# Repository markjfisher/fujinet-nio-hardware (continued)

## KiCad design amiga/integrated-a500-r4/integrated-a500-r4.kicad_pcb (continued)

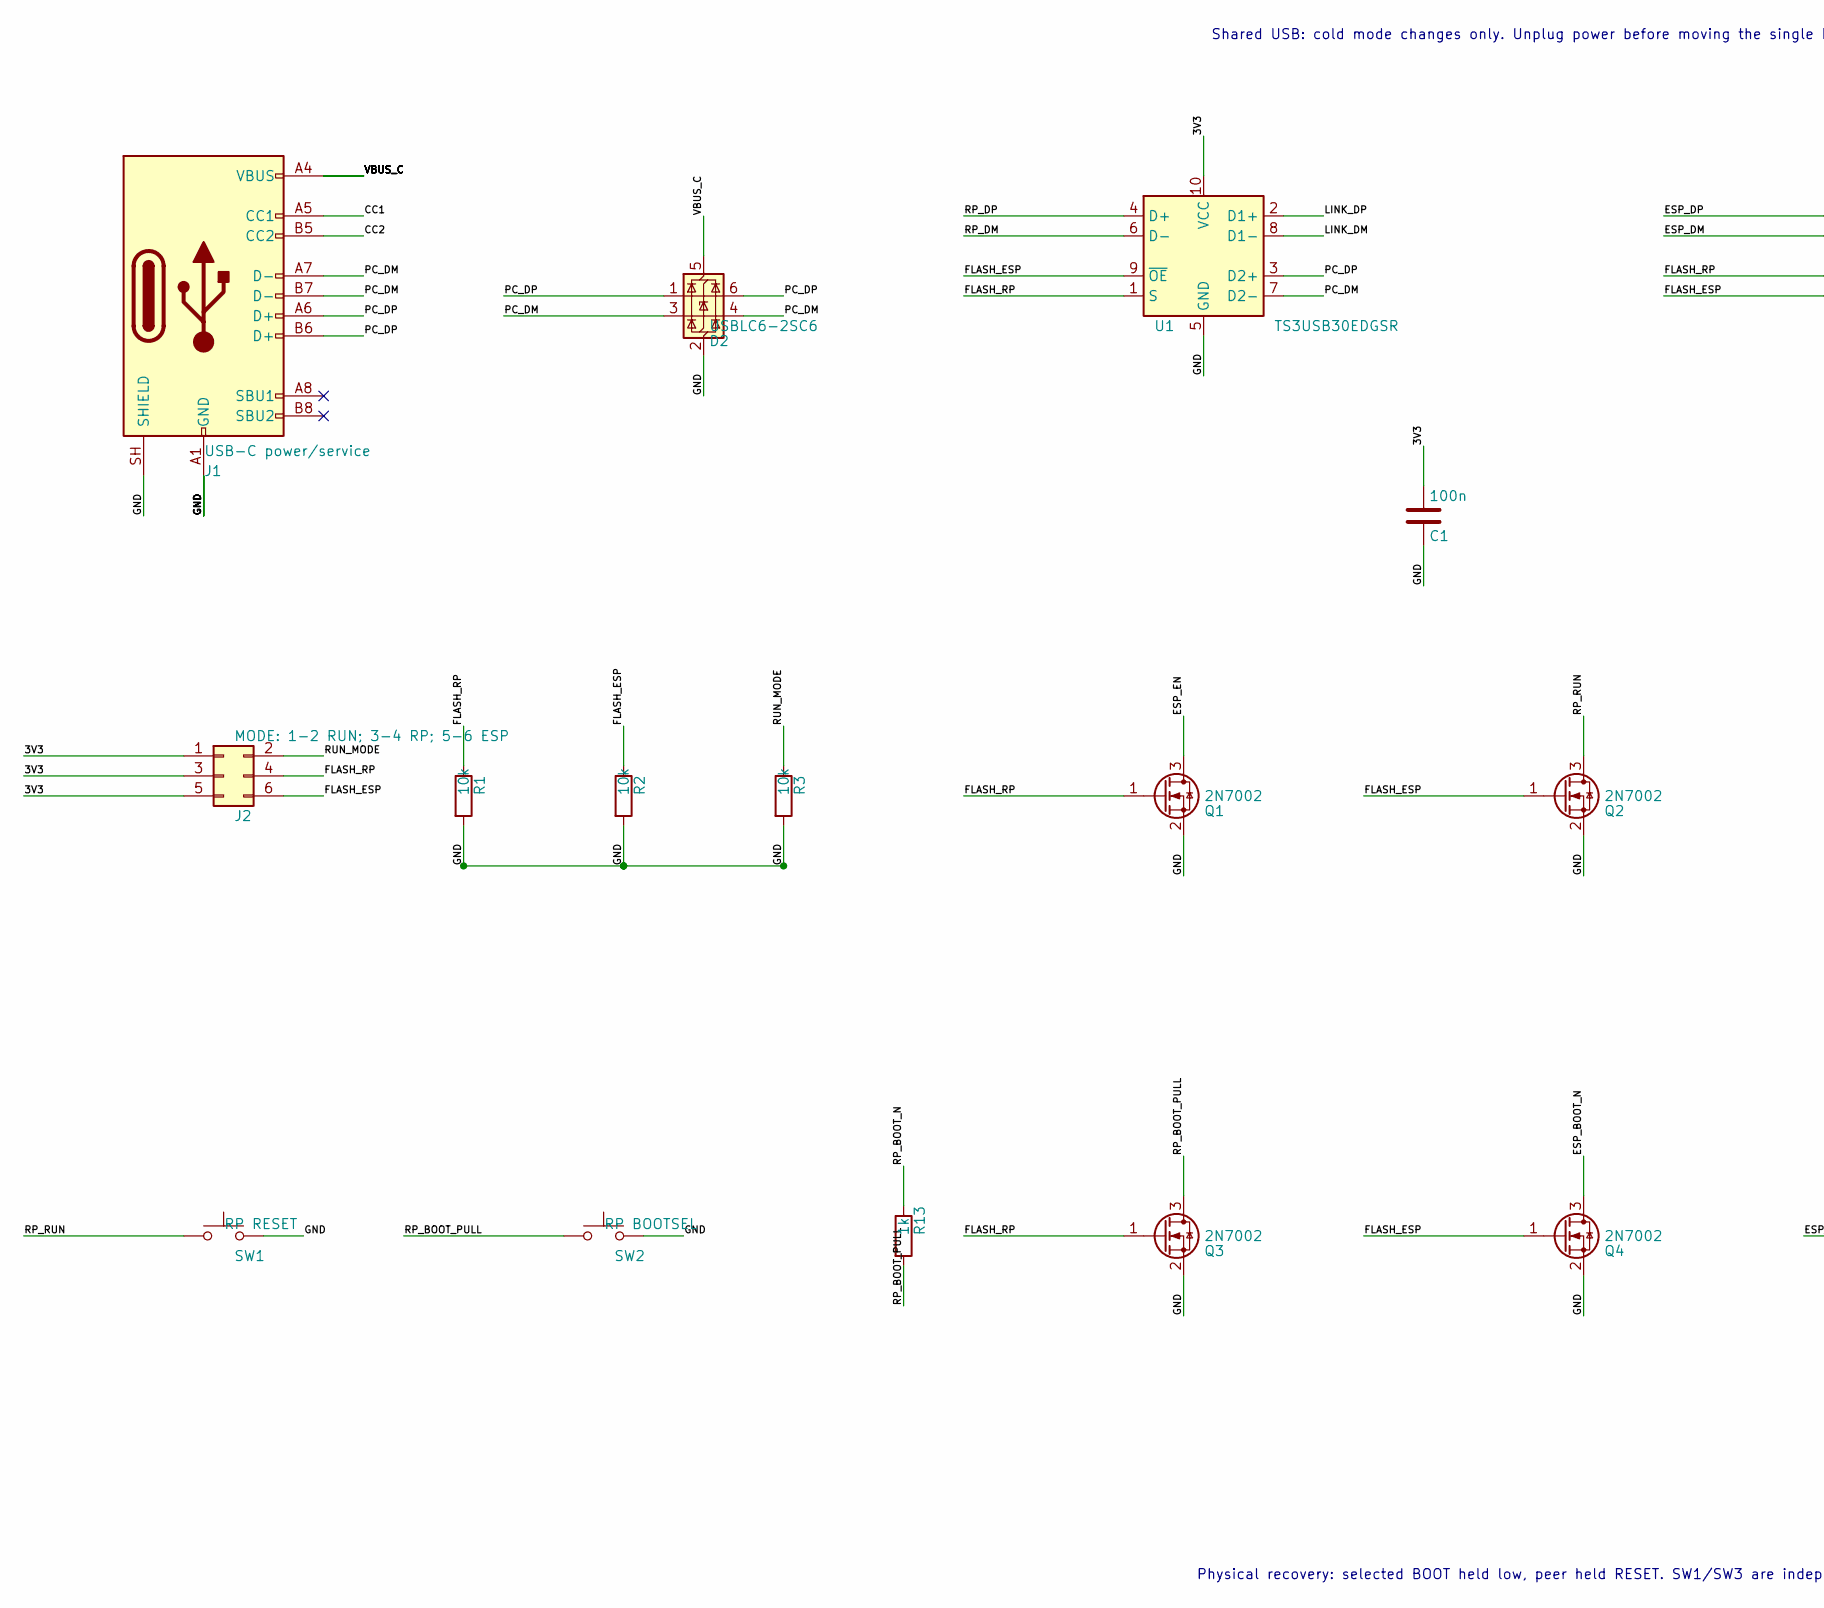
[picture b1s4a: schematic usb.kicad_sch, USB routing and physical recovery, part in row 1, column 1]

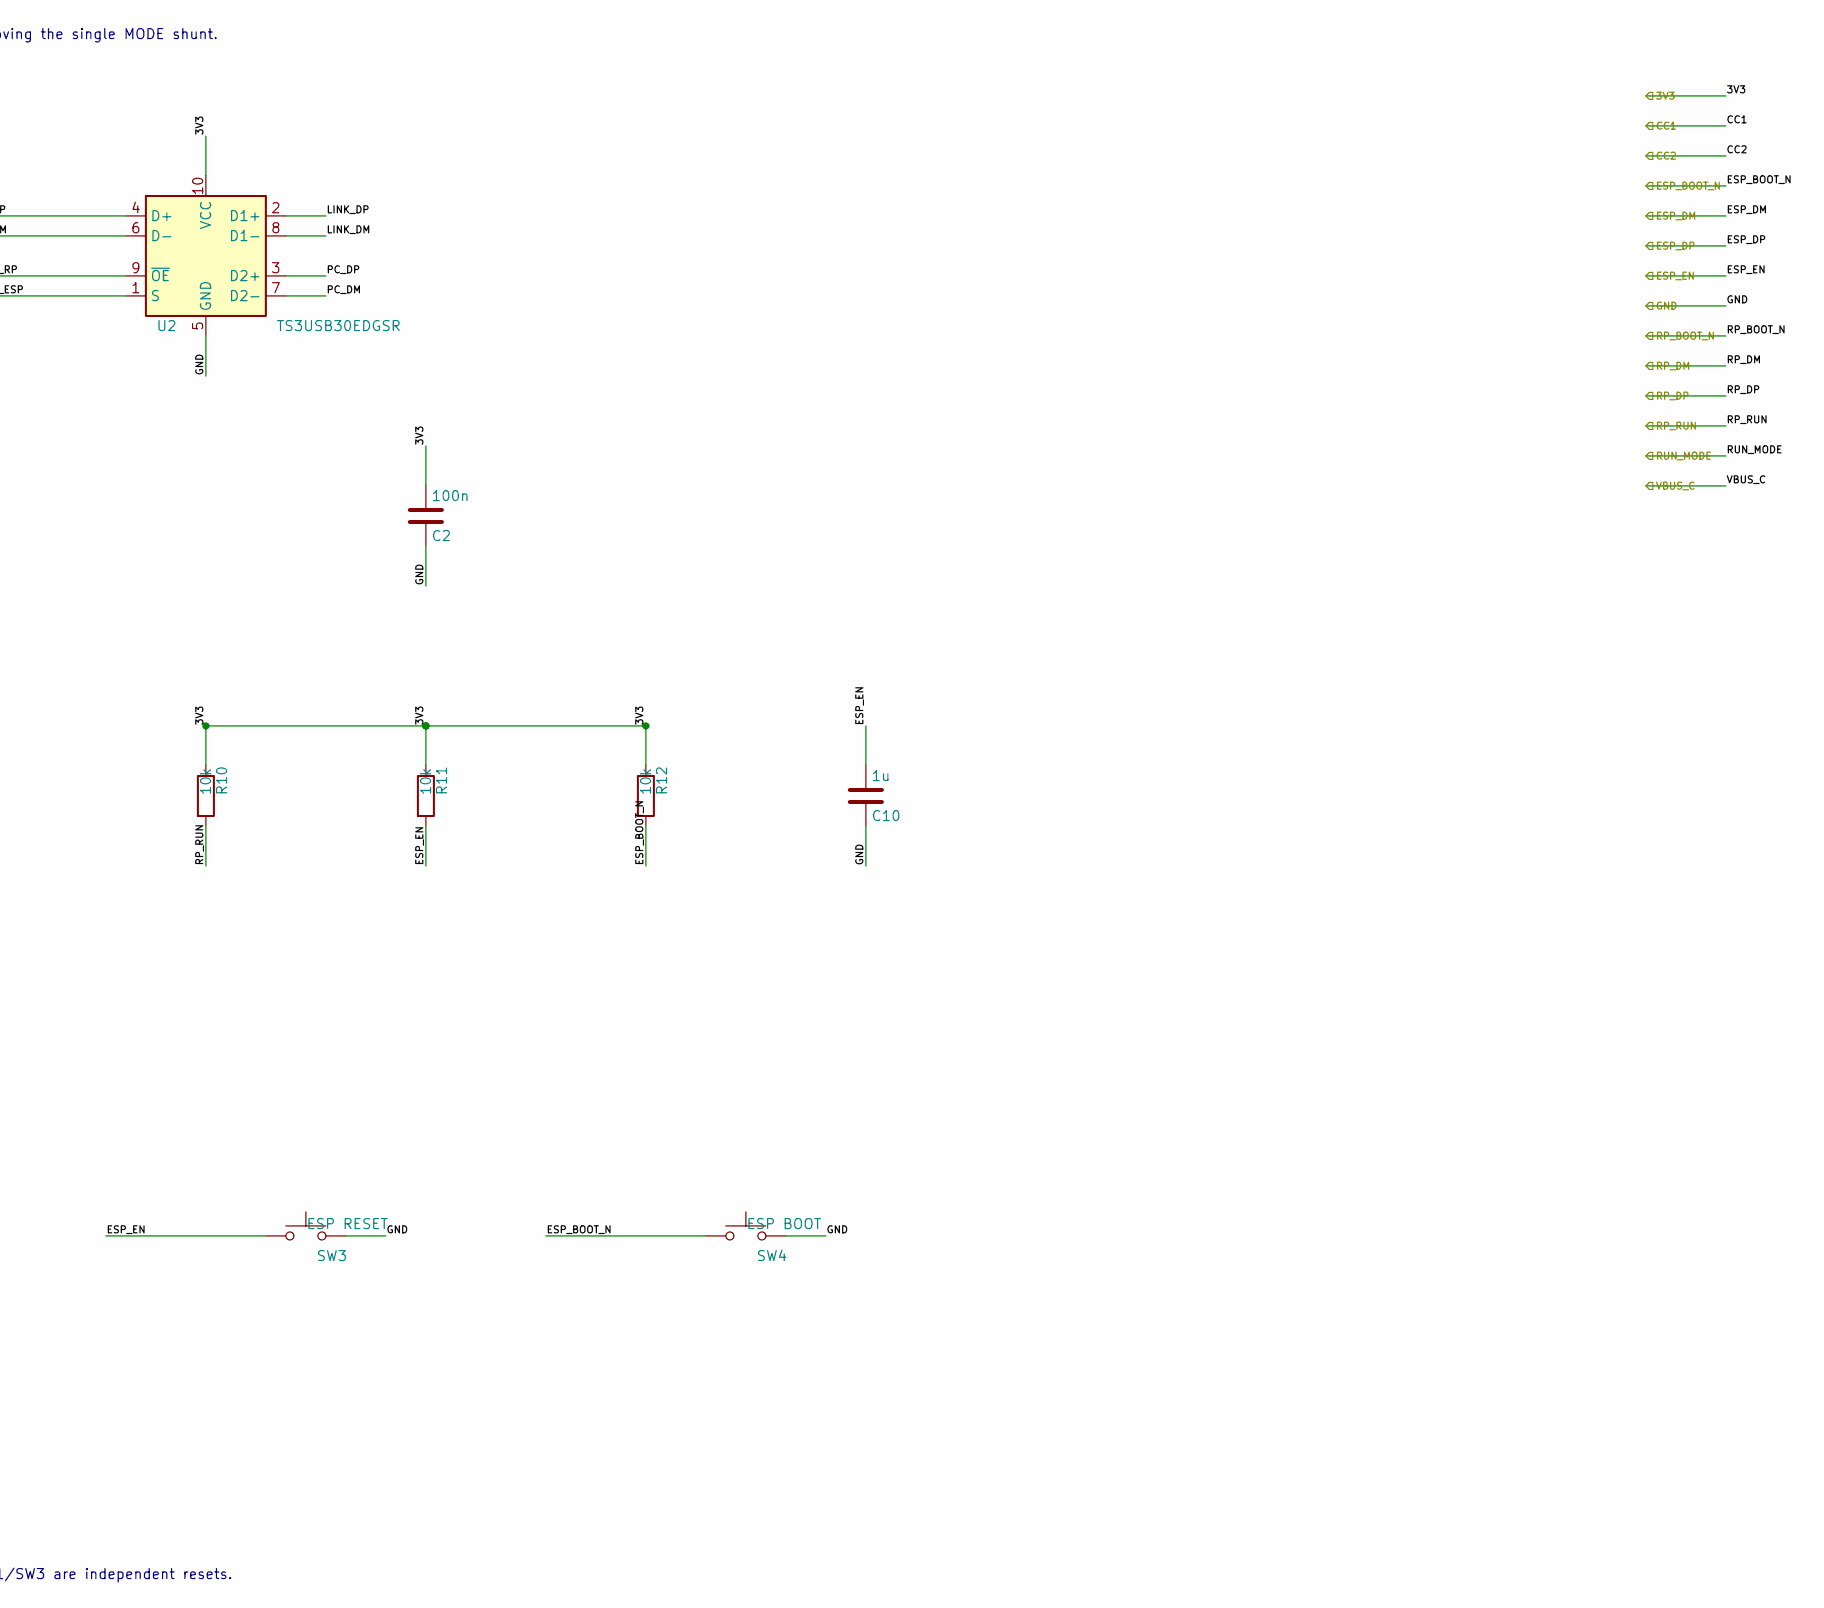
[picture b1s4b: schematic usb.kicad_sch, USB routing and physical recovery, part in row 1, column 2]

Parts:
C1, C2: 100n; C_0603_1608Metric
C10: 1u; C_0603_1608Metric
D2: USBLC6-2SC6
J1: USB-C power/service
J2: MODE: 1-2 RUN; 3-4 RP; 5-6 ESP
Q1, Q2, Q3, Q4: 2N7002
R1, R2, R3, R10, R11, R12: 10k; R_0603_1608Metric
R13: 1k; R_0603_1608Metric
SW1: RP RESET
SW2: RP BOOTSEL
SW3: ESP RESET
SW4: ESP BOOT
U1, U2: TS3USB30EDGSR

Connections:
/3V3: C1.1, C2.1, J2.1, J2.3, J2.5, R10.1, R11.1, R12.1, U1.10 (VCC), U2.10 (VCC); also elsewhere on the board
/CC1: J1.A5 (CC1); also elsewhere on the board
/CC2: J1.B5 (CC2); also elsewhere on the board
/ESP_BOOT_N: Q4.3 (D), R12.2, SW4.1; also elsewhere on the board
/ESP_DM: U2.6 (D-); also elsewhere on the board
/ESP_DP: U2.4 (D+); also elsewhere on the board
/ESP_EN: C10.1, Q1.3 (D), R11.2, SW3.1; also elsewhere on the board
/RP_BOOT_N: R13.1; also elsewhere on the board
/RP_DM: U1.6 (D-); also elsewhere on the board
/RP_DP: U1.4 (D+); also elsewhere on the board
/RP_RUN: Q2.3 (D), R10.2, SW1.1; also elsewhere on the board
/RUN_MODE: J2.2, R3.1; also elsewhere on the board
/USB routing and physical recovery/FLASH_ESP: J2.6, Q2.1 (G), Q4.1 (G), R2.1, U1.9 (~OE), U2.1 (S)
/USB routing and physical recovery/FLASH_RP: J2.4, Q1.1 (G), Q3.1 (G), R1.1, U1.1 (S), U2.9 (~OE)
/USB routing and physical recovery/LINK_DM: U1.8 (D1-), U2.8 (D1-)
/USB routing and physical recovery/LINK_DP: U1.2 (D1+), U2.2 (D1+)
/USB routing and physical recovery/PC_DM: D2.3 (I/O2), D2.4 (I/O2), J1.A7 (D-), J1.B7 (D-), U1.7 (D2-), U2.7 (D2-)
/USB routing and physical recovery/PC_DP: D2.1 (I/O1), D2.6 (I/O1), J1.A6 (D+), J1.B6 (D+), U1.3 (D2+), U2.3 (D2+)
/USB routing and physical recovery/RP_BOOT_PULL: Q3.3 (D), R13.2, SW2.1

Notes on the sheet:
Shared USB: cold mode changes only. Unplug power before moving the single MODE shunt.
Physical recovery: selected BOOT held low, peer held RESET. SW1/SW3 are independent resets.

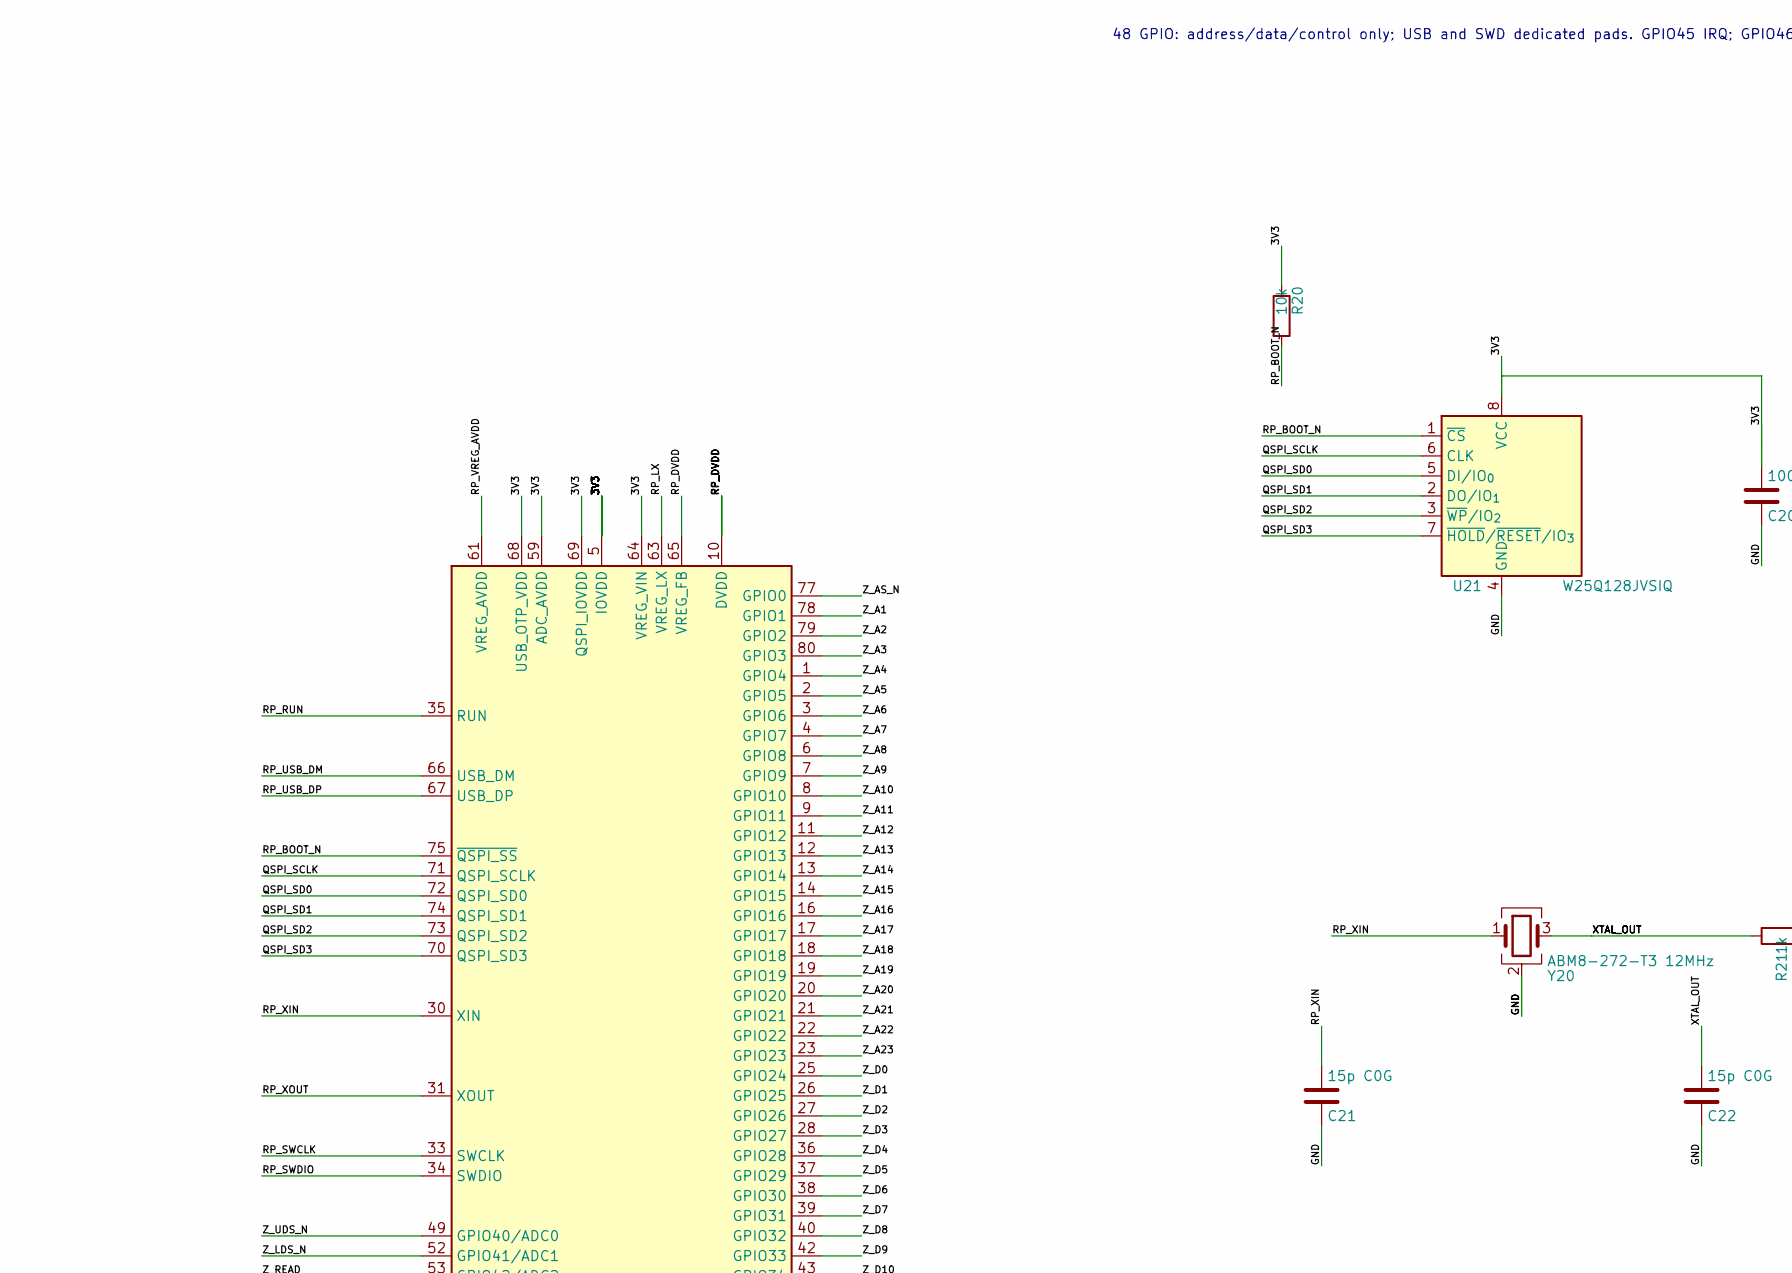
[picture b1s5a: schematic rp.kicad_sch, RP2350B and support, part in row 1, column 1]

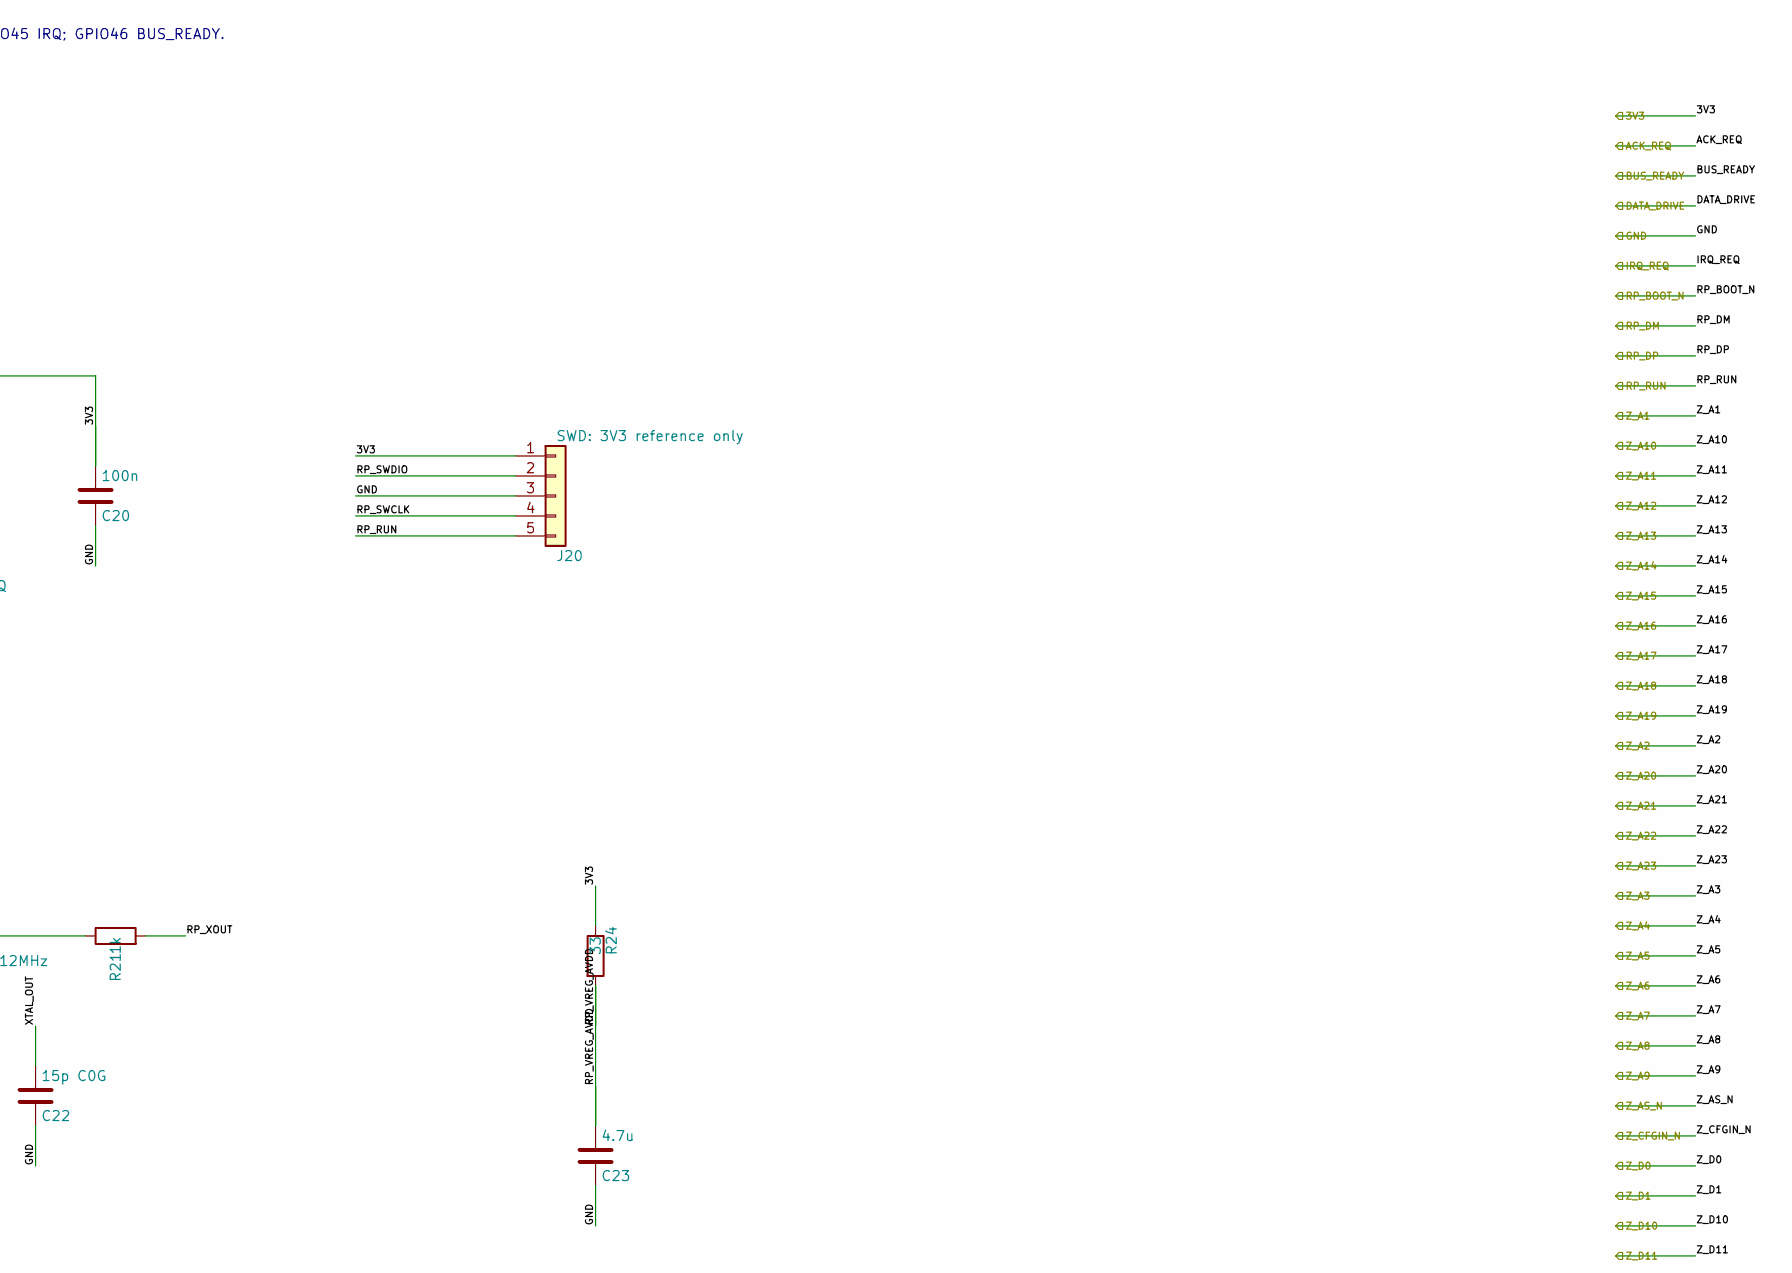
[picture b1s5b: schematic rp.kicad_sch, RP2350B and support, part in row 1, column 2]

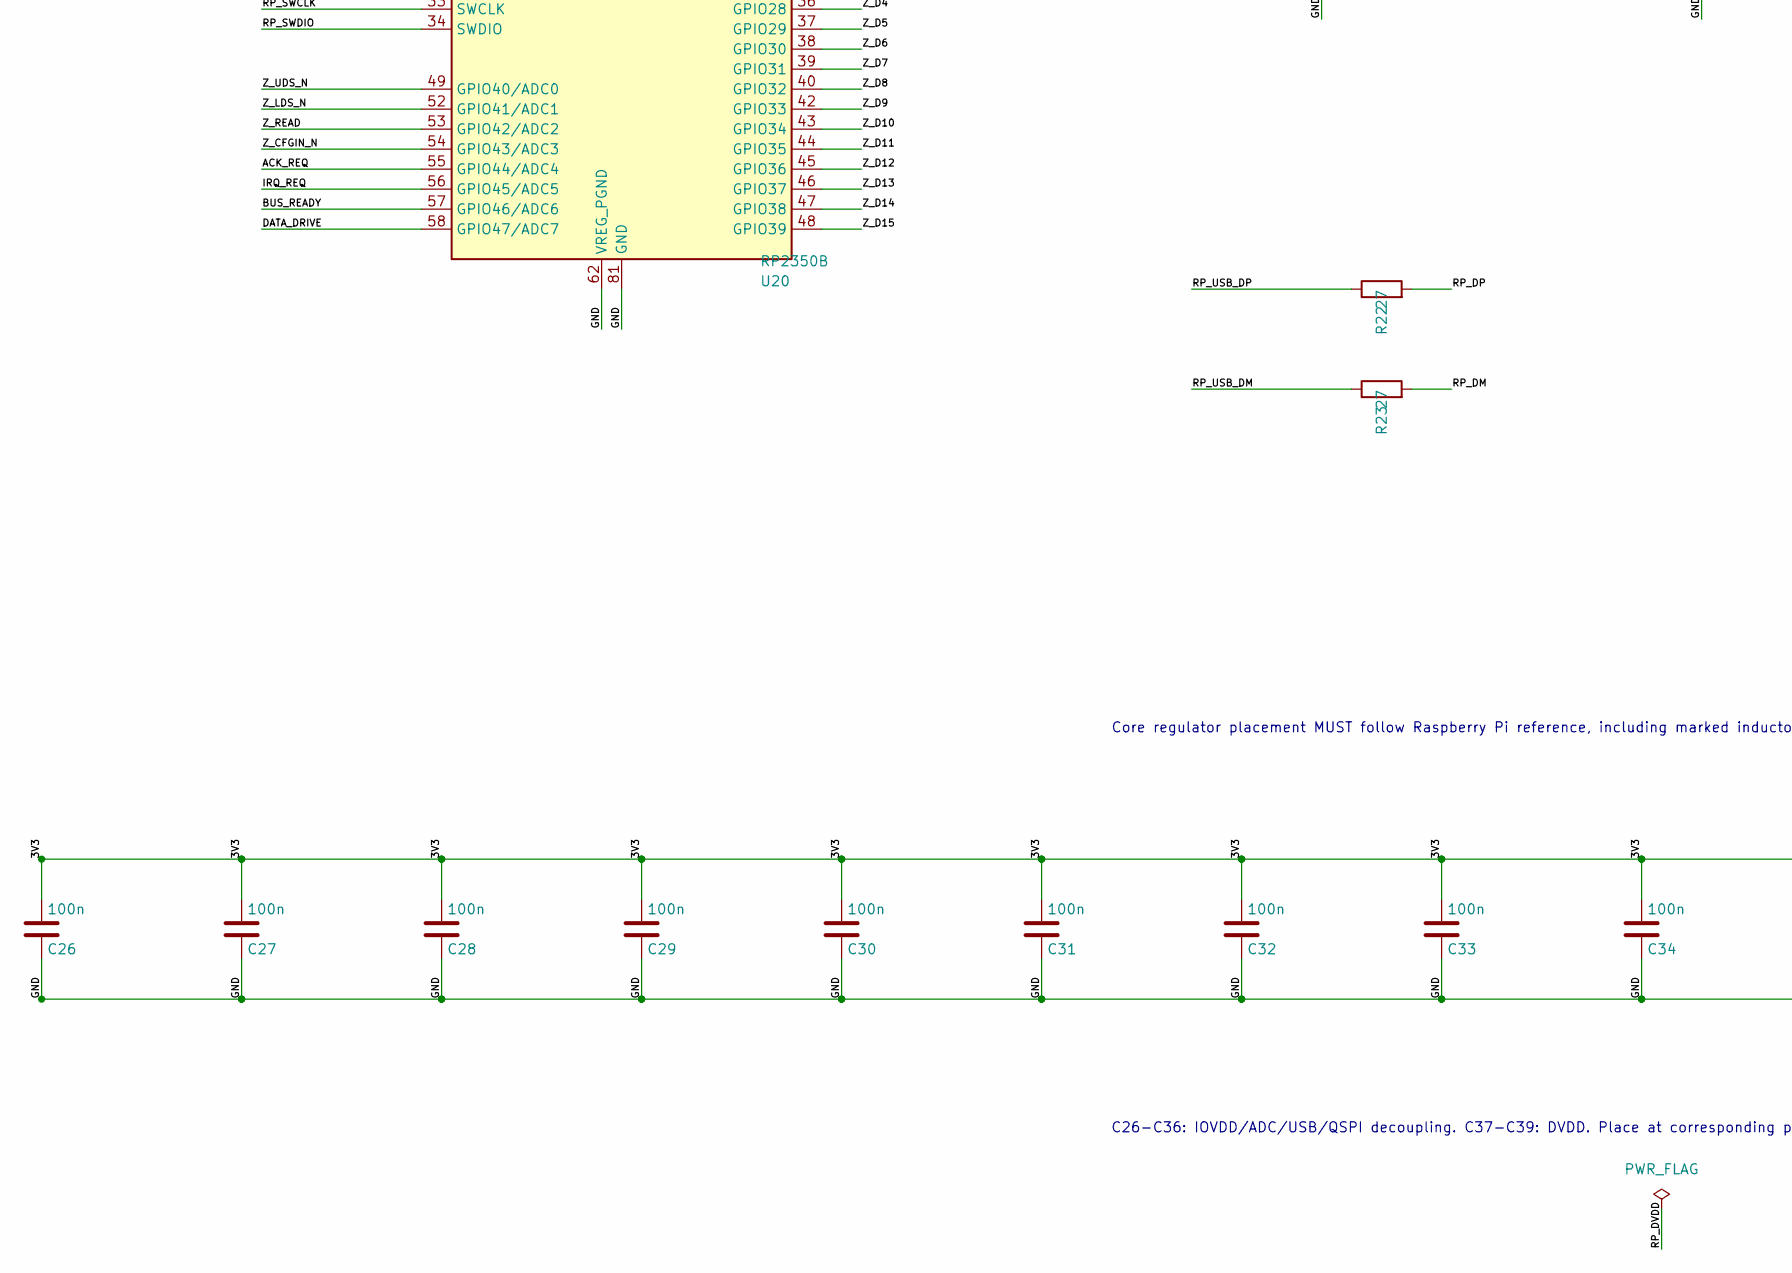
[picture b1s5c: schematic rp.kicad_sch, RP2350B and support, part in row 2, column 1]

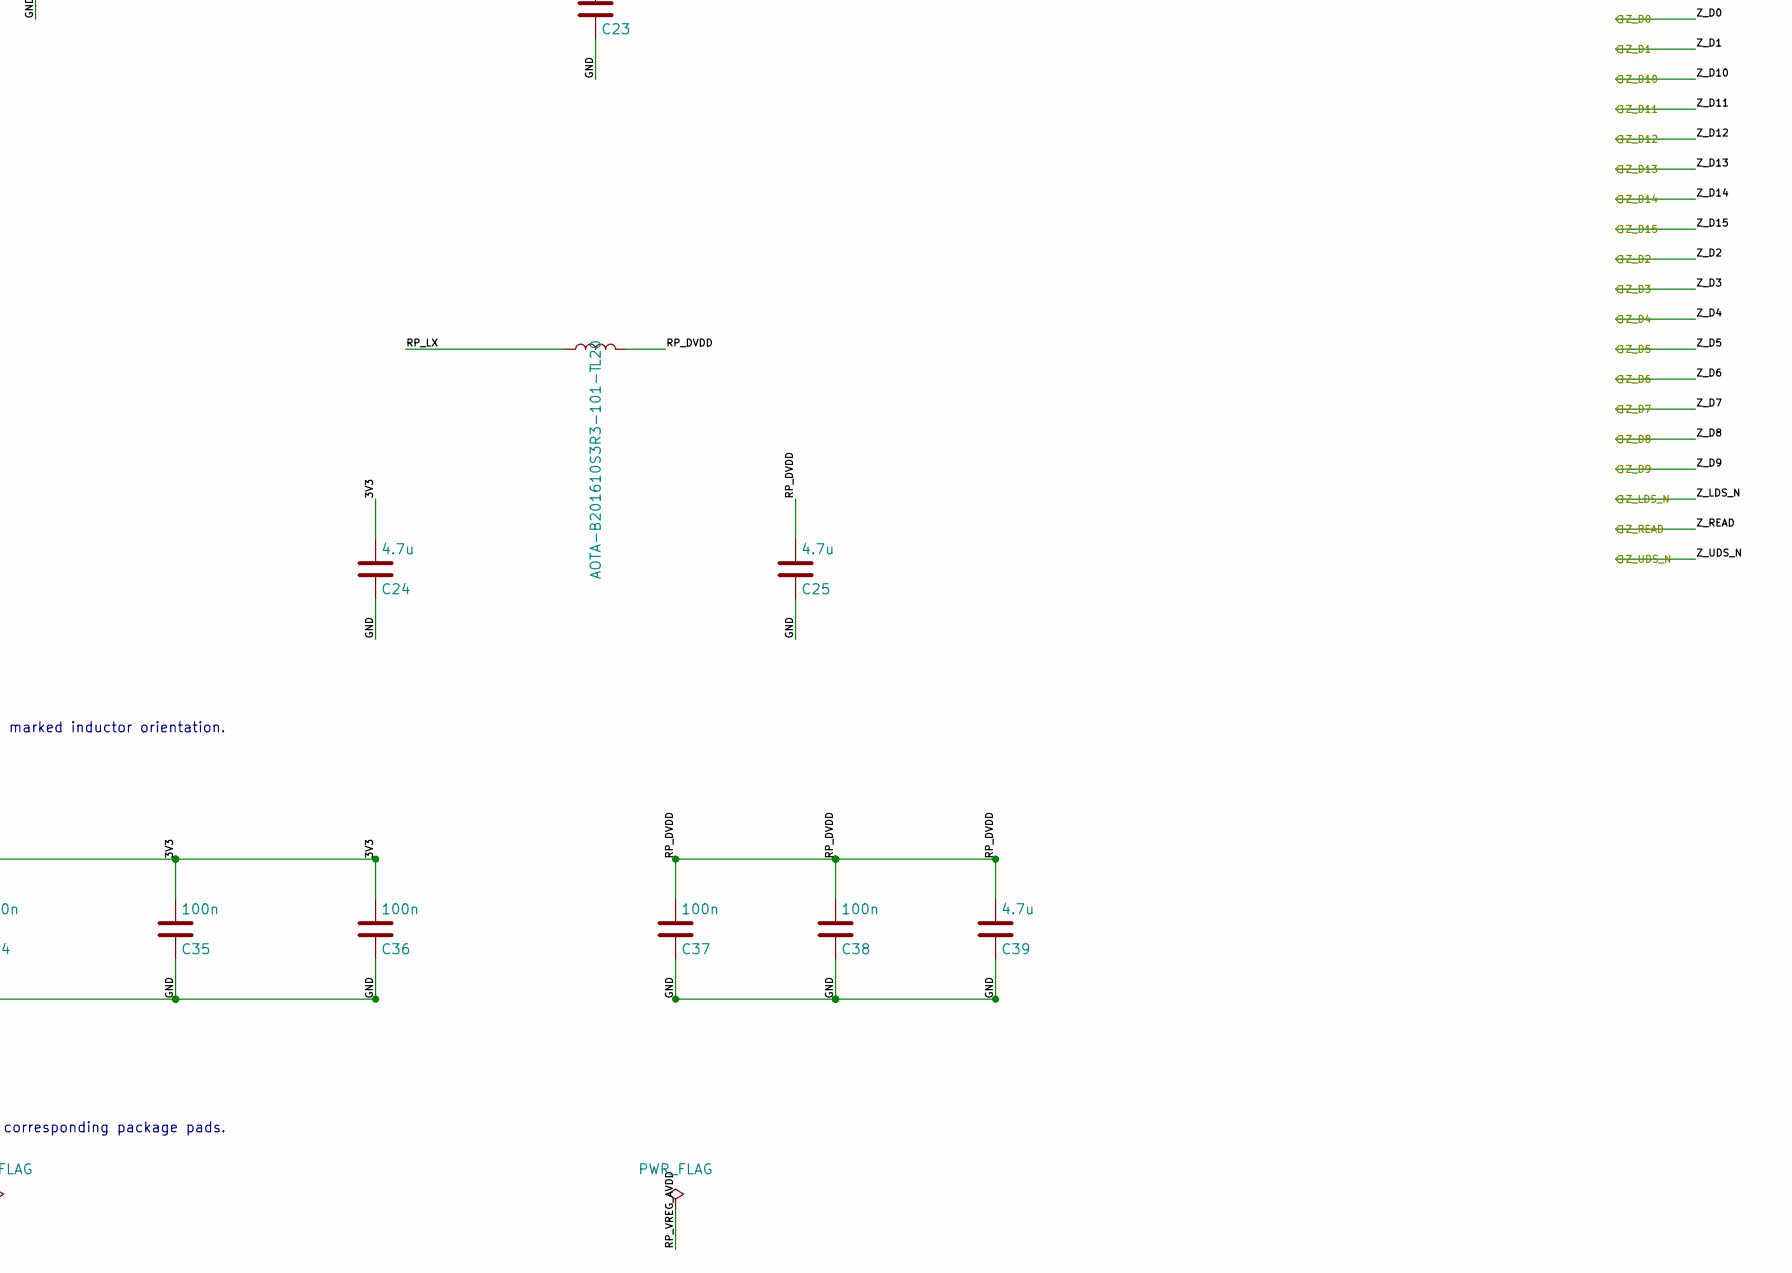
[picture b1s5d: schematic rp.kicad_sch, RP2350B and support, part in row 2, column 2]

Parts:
C20, C26, C27, C28, C29, C30, C31, C32, C33, C34, C35, C36, C37, C38: 100n; C_0603_1608Metric
C21, C22: 15p C0G; C_0603_1608Metric
C23: 4.7u; RP_Reference_C9
C24: 4.7u; RP_Reference_C6
C25: 4.7u; RP_Reference_C7
C39: 4.7u; C_0603_1608Metric
J20: SWD: 3V3 reference only; PinHeader_1x05_P2.54mm_Vertical
L20: AOTA-B201610S3R3-101-T; RP_Reference_L1
R20: 10k; R_0603_1608Metric
R21: 1k; R_0603_1608Metric
R22, R23: 27; R_0603_1608Metric
R24: 33; RP_Reference_R3
U20: RP2350B; RP_Reference_U1
U21: W25Q128JVSIQ; SOIC-8_5.3x5.3mm_P1.27mm
Y20: ABM8-272-T3 12MHz; Crystal_SMD_3225-4Pin_3.2x2.5mm

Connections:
/3V3: C20.1, C24.1, C26.1, C27.1, C28.1, C29.1, C30.1, C31.1, C32.1, C33.1, C34.1, C35.1, C36.1, J20.1, R20.1, R24.1, U20.5 (IOVDD), U20.15 (IOVDD), U20.24 (IOVDD), U20.29 (IOVDD), U20.41 (IOVDD), U20.50 (IOVDD), U20.59 (ADC_AVDD), U20.60 (IOVDD), U20.64 (VREG_VIN), U20.68 (USB_OTP_VDD), U20.69 (QSPI_IOVDD), U20.76 (IOVDD), U21.8 (VCC); also elsewhere on the board
/ACK_REQ: U20.55 (GPIO44/ADC4); also elsewhere on the board
/BUS_READY: U20.57 (GPIO46/ADC6); also elsewhere on the board
/IRQ_REQ: U20.56 (GPIO45/ADC5); also elsewhere on the board
/RP2350B and support/QSPI_SCLK: U20.71 (QSPI_SCLK), U21.6 (CLK)
/RP2350B and support/QSPI_SD0: U20.72 (QSPI_SD0), U21.5 (DI/IO_{0})
/RP2350B and support/QSPI_SD1: U20.74 (QSPI_SD1), U21.2 (DO/IO_{1})
/RP2350B and support/QSPI_SD2: U20.73 (QSPI_SD2), U21.3 (~WP/IO_{2})
/RP2350B and support/QSPI_SD3: U20.70 (QSPI_SD3), U21.7 (~HOLD/~RESET/IO_{3})
/RP2350B and support/RP_DVDD: C25.1, C37.1, C38.1, C39.1, L20.2, U20.10 (DVDD), U20.32 (DVDD), U20.51 (DVDD), U20.65 (VREG_FB)
/RP2350B and support/RP_LX: L20.1, U20.63 (VREG_LX)
/RP2350B and support/RP_SWCLK: J20.4, U20.33 (SWCLK)
/RP2350B and support/RP_SWDIO: J20.2, U20.34 (SWDIO)
/RP2350B and support/RP_USB_DM: R23.1, U20.66 (USB_DM)
/RP2350B and support/RP_USB_DP: R22.1, U20.67 (USB_DP)
/RP2350B and support/RP_VREG_AVDD: C23.1, R24.2, U20.61 (VREG_AVDD)
/RP2350B and support/RP_XIN: C21.1, U20.30 (XIN), Y20.1
/RP2350B and support/RP_XOUT: R21.2, U20.31 (XOUT)
/RP2350B and support/XTAL_OUT: C22.1, R21.1, Y20.3
/RP_BOOT_N: R20.2, U20.75 (~QSPI_SS), U21.1 (~CS); also elsewhere on the board
/RP_DM: R23.2; also elsewhere on the board
/RP_DP: R22.2; also elsewhere on the board
/RP_RUN: J20.5, U20.35 (RUN); also elsewhere on the board
/Z_A1: U20.78 (GPIO1); also elsewhere on the board
/Z_A2: U20.79 (GPIO2); also elsewhere on the board
/Z_A3: U20.80 (GPIO3); also elsewhere on the board
/Z_A4: U20.1 (GPIO4); also elsewhere on the board
/Z_A5: U20.2 (GPIO5); also elsewhere on the board
/Z_A6: U20.3 (GPIO6); also elsewhere on the board
/Z_A7: U20.4 (GPIO7); also elsewhere on the board
/Z_A8: U20.6 (GPIO8); also elsewhere on the board
/Z_A9: U20.7 (GPIO9); also elsewhere on the board
/Z_A10: U20.8 (GPIO10); also elsewhere on the board
/Z_A11: U20.9 (GPIO11); also elsewhere on the board
/Z_A12: U20.11 (GPIO12); also elsewhere on the board
/Z_A13: U20.12 (GPIO13); also elsewhere on the board
/Z_A14: U20.13 (GPIO14); also elsewhere on the board
/Z_A15: U20.14 (GPIO15); also elsewhere on the board
/Z_A16: U20.16 (GPIO16); also elsewhere on the board
/Z_A17: U20.17 (GPIO17); also elsewhere on the board
/Z_A18: U20.18 (GPIO18); also elsewhere on the board
/Z_A19: U20.19 (GPIO19); also elsewhere on the board
/Z_A20: U20.20 (GPIO20); also elsewhere on the board
/Z_A21: U20.21 (GPIO21); also elsewhere on the board
/Z_A22: U20.22 (GPIO22); also elsewhere on the board
/Z_A23: U20.23 (GPIO23); also elsewhere on the board
/Z_AS_N: U20.77 (GPIO0); also elsewhere on the board
/Z_CFGIN_N: U20.54 (GPIO43/ADC3); also elsewhere on the board
/Z_D0: U20.25 (GPIO24); also elsewhere on the board
/Z_D1: U20.26 (GPIO25); also elsewhere on the board
/Z_D2: U20.27 (GPIO26); also elsewhere on the board
/Z_D3: U20.28 (GPIO27); also elsewhere on the board
/Z_D4: U20.36 (GPIO28); also elsewhere on the board
/Z_D5: U20.37 (GPIO29); also elsewhere on the board
/Z_D6: U20.38 (GPIO30); also elsewhere on the board
/Z_D7: U20.39 (GPIO31); also elsewhere on the board
/Z_D8: U20.40 (GPIO32); also elsewhere on the board
/Z_D9: U20.42 (GPIO33); also elsewhere on the board
/Z_D10: U20.43 (GPIO34); also elsewhere on the board
/Z_D11: U20.44 (GPIO35); also elsewhere on the board
/Z_D12: U20.45 (GPIO36); also elsewhere on the board
/Z_D13: U20.46 (GPIO37); also elsewhere on the board
/Z_D14: U20.47 (GPIO38); also elsewhere on the board
/Z_D15: U20.48 (GPIO39); also elsewhere on the board
/Z_LDS_N: U20.52 (GPIO41/ADC1); also elsewhere on the board
/Z_READ: U20.53 (GPIO42/ADC2); also elsewhere on the board
/Z_UDS_N: U20.49 (GPIO40/ADC0); also elsewhere on the board

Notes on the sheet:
48 GPIO: address/data/control only; USB and SWD dedicated pads. GPIO45 IRQ; GPIO46 BUS_READY.
Core regulator placement MUST follow Raspberry Pi reference, including marked inductor orientation.
C26-C36: IOVDD/ADC/USB/QSPI decoupling. C37-C39: DVDD. Place at corresponding package pads.
